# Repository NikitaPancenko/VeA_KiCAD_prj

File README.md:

# VeA_KiCAD_prj

Šīs repozitorijs ir paredzēts kursa projektiem.

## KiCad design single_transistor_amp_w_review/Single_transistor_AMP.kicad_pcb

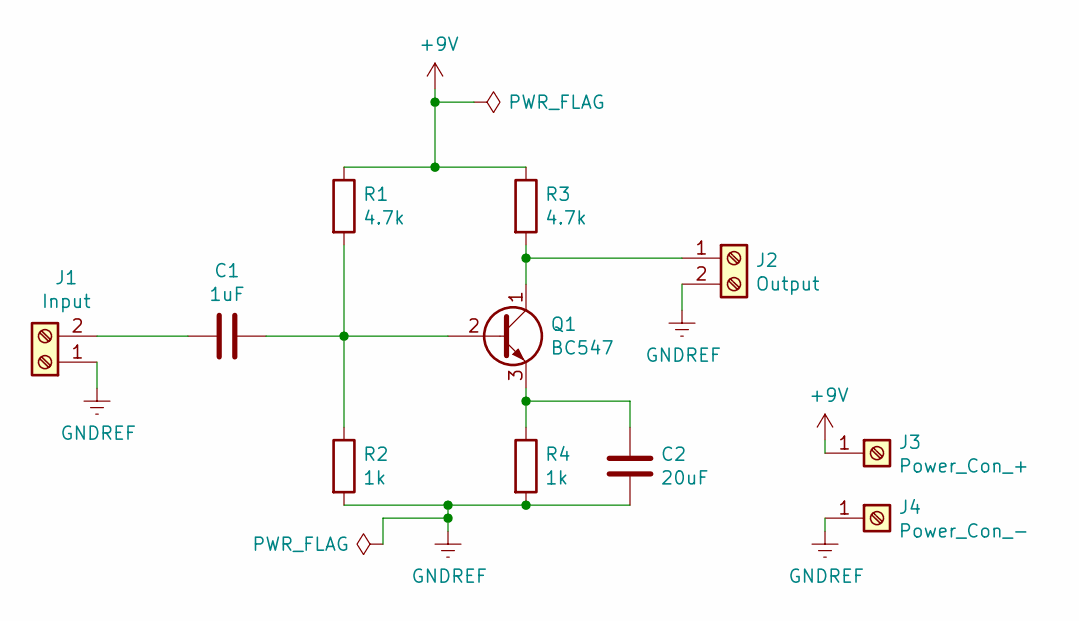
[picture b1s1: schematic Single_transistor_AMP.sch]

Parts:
C1: 1uF; C_Radial_D5.0mm_H11.0mm_P2.00mm
C2: 20uF; C_Radial_D5.0mm_H11.0mm_P2.00mm
J1: Input; TerminalBlock_Altech_AK300-2_P5.00mm
J2: Output; TerminalBlock_Altech_AK300-2_P5.00mm
J3: Power_Con_+; Banana_Jack_1Pin
J4: Power_Con_-; Banana_Jack_1Pin
Q1: BC547; TO-92_Inline
R1, R3: 4.7k; R_Axial_DIN0204_L3.6mm_D1.6mm_P7.62mm_Horizontal
R2, R4: 1k; R_Axial_DIN0204_L3.6mm_D1.6mm_P7.62mm_Horizontal

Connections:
+9V: J3.1, R1.1, R3.1
GNDREF: C2.1, J1.1, J2.2, J4.1, R2.2, R4.2
unnamed: C1.1, Q1.2 (B), R1.2, R2.1
unnamed: C1.2, J1.2
unnamed: C2.2, Q1.3 (E), R4.1
unnamed: J2.1, Q1.1 (C), R3.2

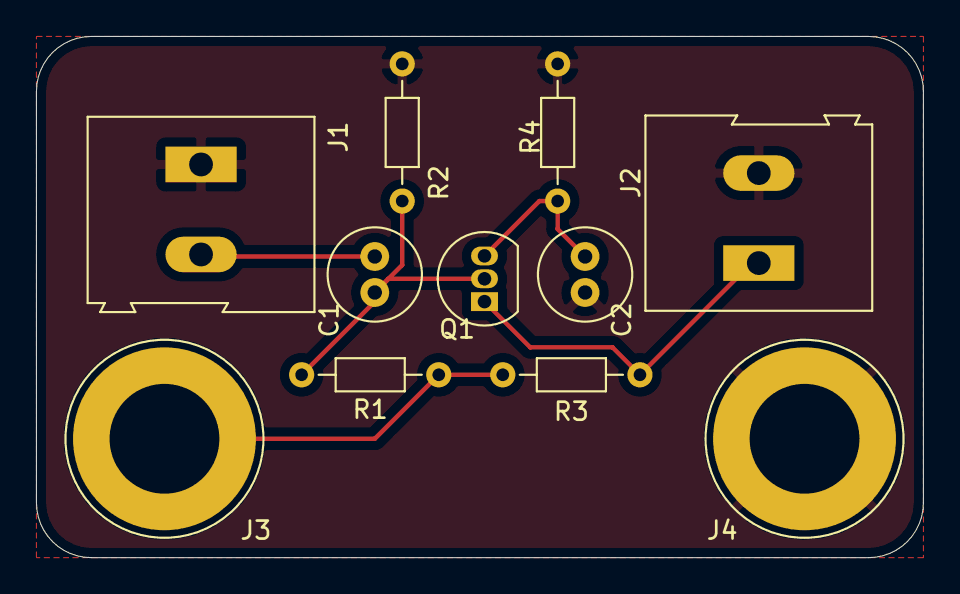
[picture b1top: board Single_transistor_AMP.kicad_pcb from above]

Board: 2 copper layers, 49.3 x 29.0 mm, 11 parts (0 on the bottom side), 6 nets.

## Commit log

2021-09-29 README update to test
2022-01-13 maajas darbi
